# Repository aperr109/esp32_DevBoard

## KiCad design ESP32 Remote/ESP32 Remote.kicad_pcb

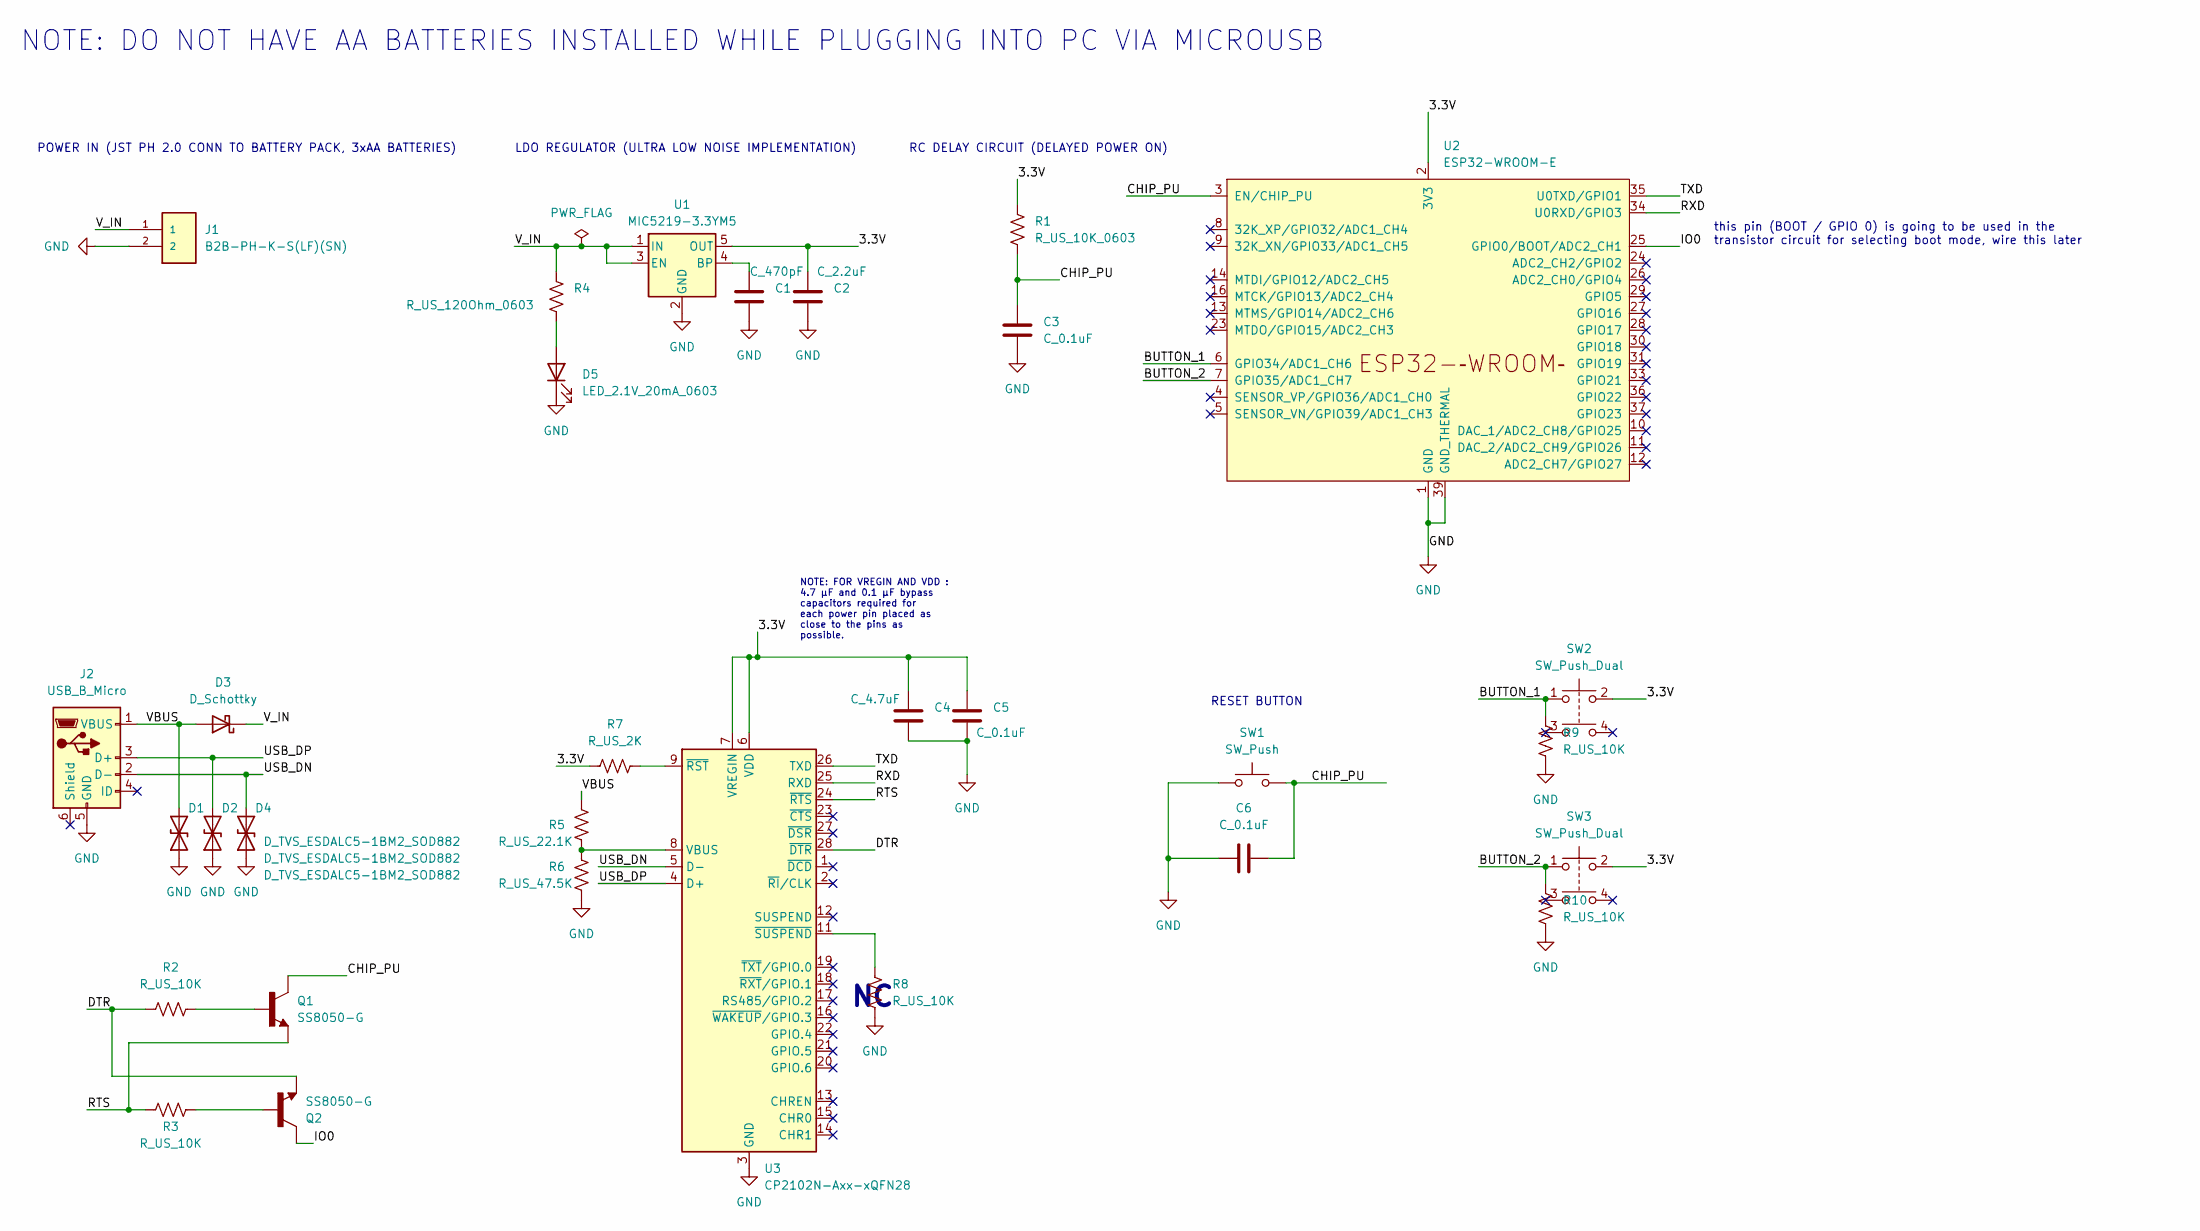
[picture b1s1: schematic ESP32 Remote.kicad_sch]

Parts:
C1: C_470pF; C_0805_2012Metric
C2: C_2.2uF; C_0805_2012Metric
C3, C5, C6: C_0.1uF; C_0805_2012Metric
C4: C_4.7uF; C_0805_2012Metric
D1, D2, D4: D_TVS_ESDALC5-1BM2_SOD882; DIO_VCUT0714A-HD1-GS08 (1)
D3: D_Schottky; SOD2513X120N
D5: LED_2.1V_20mA_0603; LED_SML-LXFM0603SIC-TR
J1: B2B-PH-K-S(LF)(SN); JST_B2B-PH-K-S(LF)(SN); PARTREV N/A; DIGI-KEY_PART_NUMBER 455-1704-ND
J2: USB_B_Micro; GCT_USB3090-XX-X_REVE
Q1, Q2: SS8050-G; TRANS_SS8050-G; PARTREV A
R1: R_US_10K_0603; R_0805_2012Metric
R2, R3, R8, R9, R10: R_US_10K; R_0805_2012Metric
R4: R_US_120Ohm_0603; R_0805_2012Metric
R5: R_US_22.1K; R_0805_2012Metric
R6: R_US_47.5K; R_0805_2012Metric
R7: R_US_2K; R_0805_2012Metric
SW1: SW_Push; SW_TS04-66-55-BK-160-SMT
SW2, SW3: SW_Push_Dual; SW_TL1100CF160Q
U1: MIC5219-3.3YM5; SOT-23-5
U2: ESP32-WROOM-E; ESP32-WROOM-32E
U3: CP2102N-Axx-xQFN28; QFN-28-1EP_5x5mm_P0.5mm_EP3.35x3.35mm

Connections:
/3.3V: C2.1, C4.1, C5.1, R1.1, R7.1, SW2.2, SW3.2, U1.5 (OUT), U2.2 (3V3), U3.6 (VDD), U3.7 (VREGIN)
/BUTTON_1: R9.1, SW2.1, U2.6 (GPIO34/ADC1_CH6)
/BUTTON_2: R10.1, SW3.1, U2.7 (GPIO35/ADC1_CH7)
/CHIP_PU: C3.1, C6.1, Q1.3, R1.2, SW1.2, U2.3 (EN/CHIP_PU)
/DTR: Q2.2, R2.1, U3.28 (~DTR)
/IO0: Q2.3, U2.25 (GPIO0/BOOT/ADC2_CH1)
/RTS: Q1.2, R3.1, U3.24 (~RTS)
/RXD: U2.34 (U0RXD/GPIO3), U3.25 (RXD)
/TXD: U2.35 (U0TXD/GPIO1), U3.26 (TXD)
/USB_DN: D4.2 (A2), J2.2 (D-), U3.5 (D-)
/USB_DP: D2.2 (A2), J2.3 (D+), U3.4 (D+)
/VBUS: D1.2 (A2), D3.2 (A), J2.1 (VBUS), R5.1
/V_IN: D3.1 (K), J1.1, R4.1, U1.1 (IN), U1.3 (EN)
GND: C1.2, C2.2, C3.2, C4.2, C5.2, C6.2, D1.1 (A1), D2.1 (A1), D4.1 (A1), D5.1 (K), J1.2, J2.5 (GND), R6.2, R8.2, R9.2, R10.2, SW1.1, U1.2 (GND), U2.1 (GND), U2.15 (GND), U2.38 (GND), U2.39 (GND_THERMAL), U3.3 (GND), U3.29 (GND)
unnamed: D5.2 (A), R4.2
unnamed: Q1.1, R2.2
unnamed: Q2.1, R3.2
unnamed: C1.1, U1.4 (BP)
unnamed: R5.2, R6.1, U3.8 (VBUS)
unnamed: R7.2, U3.9 (~RST)
unnamed: R8.1, U3.11 (~SUSPEND)

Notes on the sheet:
NOTE: DO NOT HAVE AA BATTERIES INSTALLED WHILE PLUGGING INTO PC VIA MICROUSB
RESET BUTTON
RC DELAY CIRCUIT (DELAYED POWER ON)
POWER IN (JST PH 2.0 CONN TO BATTERY PACK, 3xAA BATTERIES)
NOTE: FOR VREGIN AND VDD : 4.7 µF and 0.1 µF bypass capacitors required for each power pin placed as close to the pins as possible.
LDO REGULATOR (ULTRA LOW NOISE IMPLEMENTATION)
this pin (BOOT / GPIO 0) is going to be used in the transistor circuit for selecting boot mode, wire this later

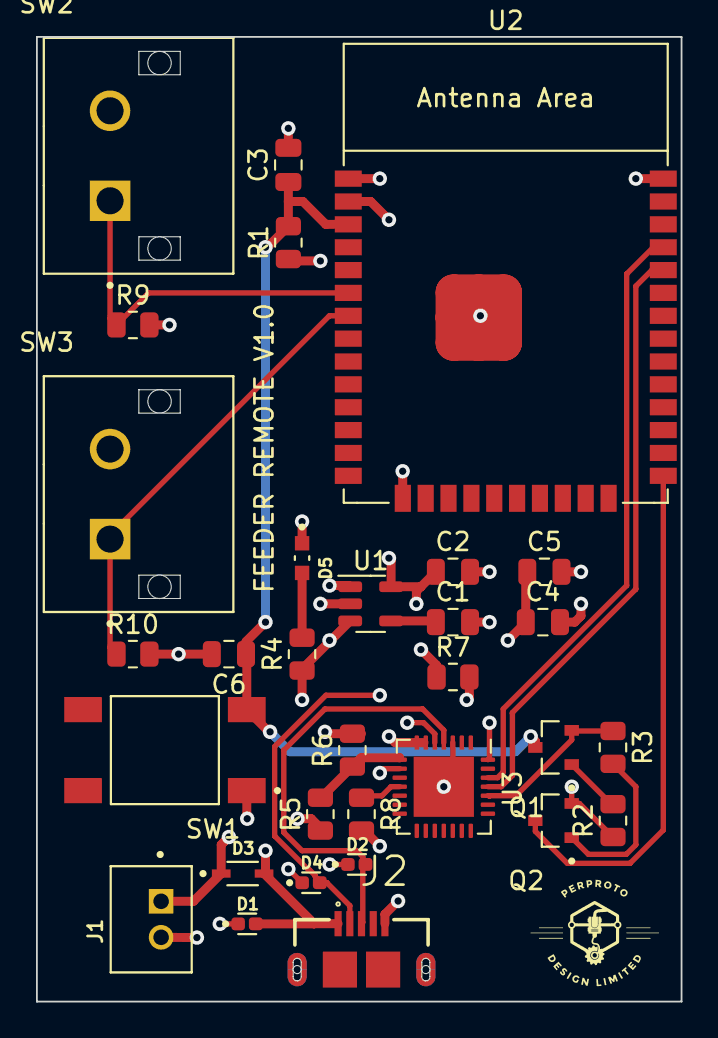
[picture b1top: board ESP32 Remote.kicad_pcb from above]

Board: 4 copper layers, 35.8 x 53.6 mm, 31 parts (0 on the bottom side), 21 nets.

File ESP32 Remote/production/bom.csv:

Designator,Footprint,Quantity,Value,LCSC Part #
C1,0805,1,C_470pF,
C2,0805,1,C_2.2uF,
"C3, C5, C6",0805,3,C_0.1uF,
C4,0805,1,C_4.7uF,
"D1, D2, D4",DIO_VCUT0714A-HD1-GS08 (1),3,D_TVS_ESDALC5-1BM2_SOD882,
D3,SOD2513X120N,1,D_Schottky,
D5,LED_SML-LXFM0603SIC-TR,1,LED_2.1V_20mA_0603,
J1,JST_B2B-PH-K-S(LF)(SN),1,B2B-PH-K-S(LF)(SN),
J2,GCT_USB3090-XX-X_REVE,1,USB_B_Micro,
"Q1, Q2",TRANS_SS8050-G,2,SS8050-G,
R1,0805,1,R_US_10K_0603,
"R10, R9",0805,2,R_US,
"R2, R3, R8",0805,3,R_US_10K,
R4,0805,1,R_US_120Ohm_0603,
R5,0805,1,R_US_22.1K,
R6,0805,1,R_US_47.5K,
R7,0805,1,R_US_2K,
SW1,SW_TS04-66-55-BK-160-SMT,1,SW_Push,
"SW2, SW3",SW_TL1100CF160Q,2,SW_Push_Dual,
U1,SOT-23-5,1,MIC5219-3.3YM5,
U2,ESP32-WROOM-32E,1,ESP32-WROOM-E,
U3,QFN-28-1EP_5x5mm_P0.5mm_EP3.35x3.35mm,1,CP2102N-Axx-xQFN28,

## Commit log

2025-07-20 transferred to github from archived folder
2025-07-20 added gitignore
2025-07-20 added proper gitignore
